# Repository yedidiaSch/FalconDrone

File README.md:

# FalconDrone - RTOS Based Flight Controller

## Project Overview
FalconDrone is an ongoing development of a quadcopter flight control system built from scratch using the **STM32F446RE (Nucleo)** platform. The project focuses on implementing high-performance real-time estimation and control algorithms within a **FreeRTOS** environment.

The current milestone focuses on a "Studio-Tethered" stabilization mode, ensuring the drone maintains its attitude (Roll/Pitch) while secured to a test bench.

## System Architecture
The firmware is designed with a modular, object-oriented approach in C++, emphasizing non-blocking operations and efficient resource management.

### Key Features
* **Real-Time Kernel:** Task management and scheduling via FreeRTOS.
* **Asynchronous I/O:** IMU (ICM-20948 or MPU6050) data acquisition using **I2C DMA** to minimize CPU overhead.
* **Thread-Safe Logging:** Custom UART logging mechanism utilizing **DMA** and FreeRTOS Queues for non-blocking telemetry.
* **Attitude Estimation:** Implementation of raw sensor data processing (Accelerometer and Gyroscope) for Roll/Pitch calculation.

## Hardware Stack
* **MCU:** STM32F446RE (ARM Cortex-M4 @ 180MHz)
* **IMU:** ICM-20948 on the carrier board (`hardware/carrier`), MPU6050 on the breadboard rig.
  Pick with `cmake --preset Debug -DFALCON_BOARD=CARRIER|BREADBOARD` (CARRIER is the default;
  it also selects the nRF24 radio, BREADBOARD the ESP-NOW bridge).
* **Frame:** F450 Quadcopter Frame
* **Motors:** A2212 1000KV Brushless Motors
* **ESCs:** 30A Brushless XXD
* **Power:** 3S Lipo 2200mAh 11.1V

## Software Stack
* **Language:** C++ / C
* **OS:** FreeRTOS
* **Framework:** STM32Cube HAL
* **Build System:** CMake
* **Development Env:** VS Code on Ubuntu

## Current Status: Attitude Estimation Phase
The system currently performs the following:
1.  Initializes hardware peripherals (I2C, UART, DMA, GPIO).
2.  Starts the FreeRTOS scheduler.
3.  Continuously streams 14-byte IMU data packets via DMA.
4.  Processes raw data into Euler angles (Roll and Pitch).

### Forthcoming Milestones
* **Sensor Fusion:** Implementation of a Complementary Filter or Kalman Filter to reduce accelerometer noise and gyroscope drift.
* **PID Control:** Development of the attitude control loop for motor speed regulation.
* **PWM Generation:** Utilizing Timer peripherals to drive ESCs.

## Setup and Installation

### Prerequisites
* GNU Arm Embedded Toolchain
* CMake (minimum 3.10)
* STM32CubeMX (for peripheral configuration)
* OpenOCD / ST-Link Utilities

### Building
```bash
mkdir build
cd build
cmake ..
make

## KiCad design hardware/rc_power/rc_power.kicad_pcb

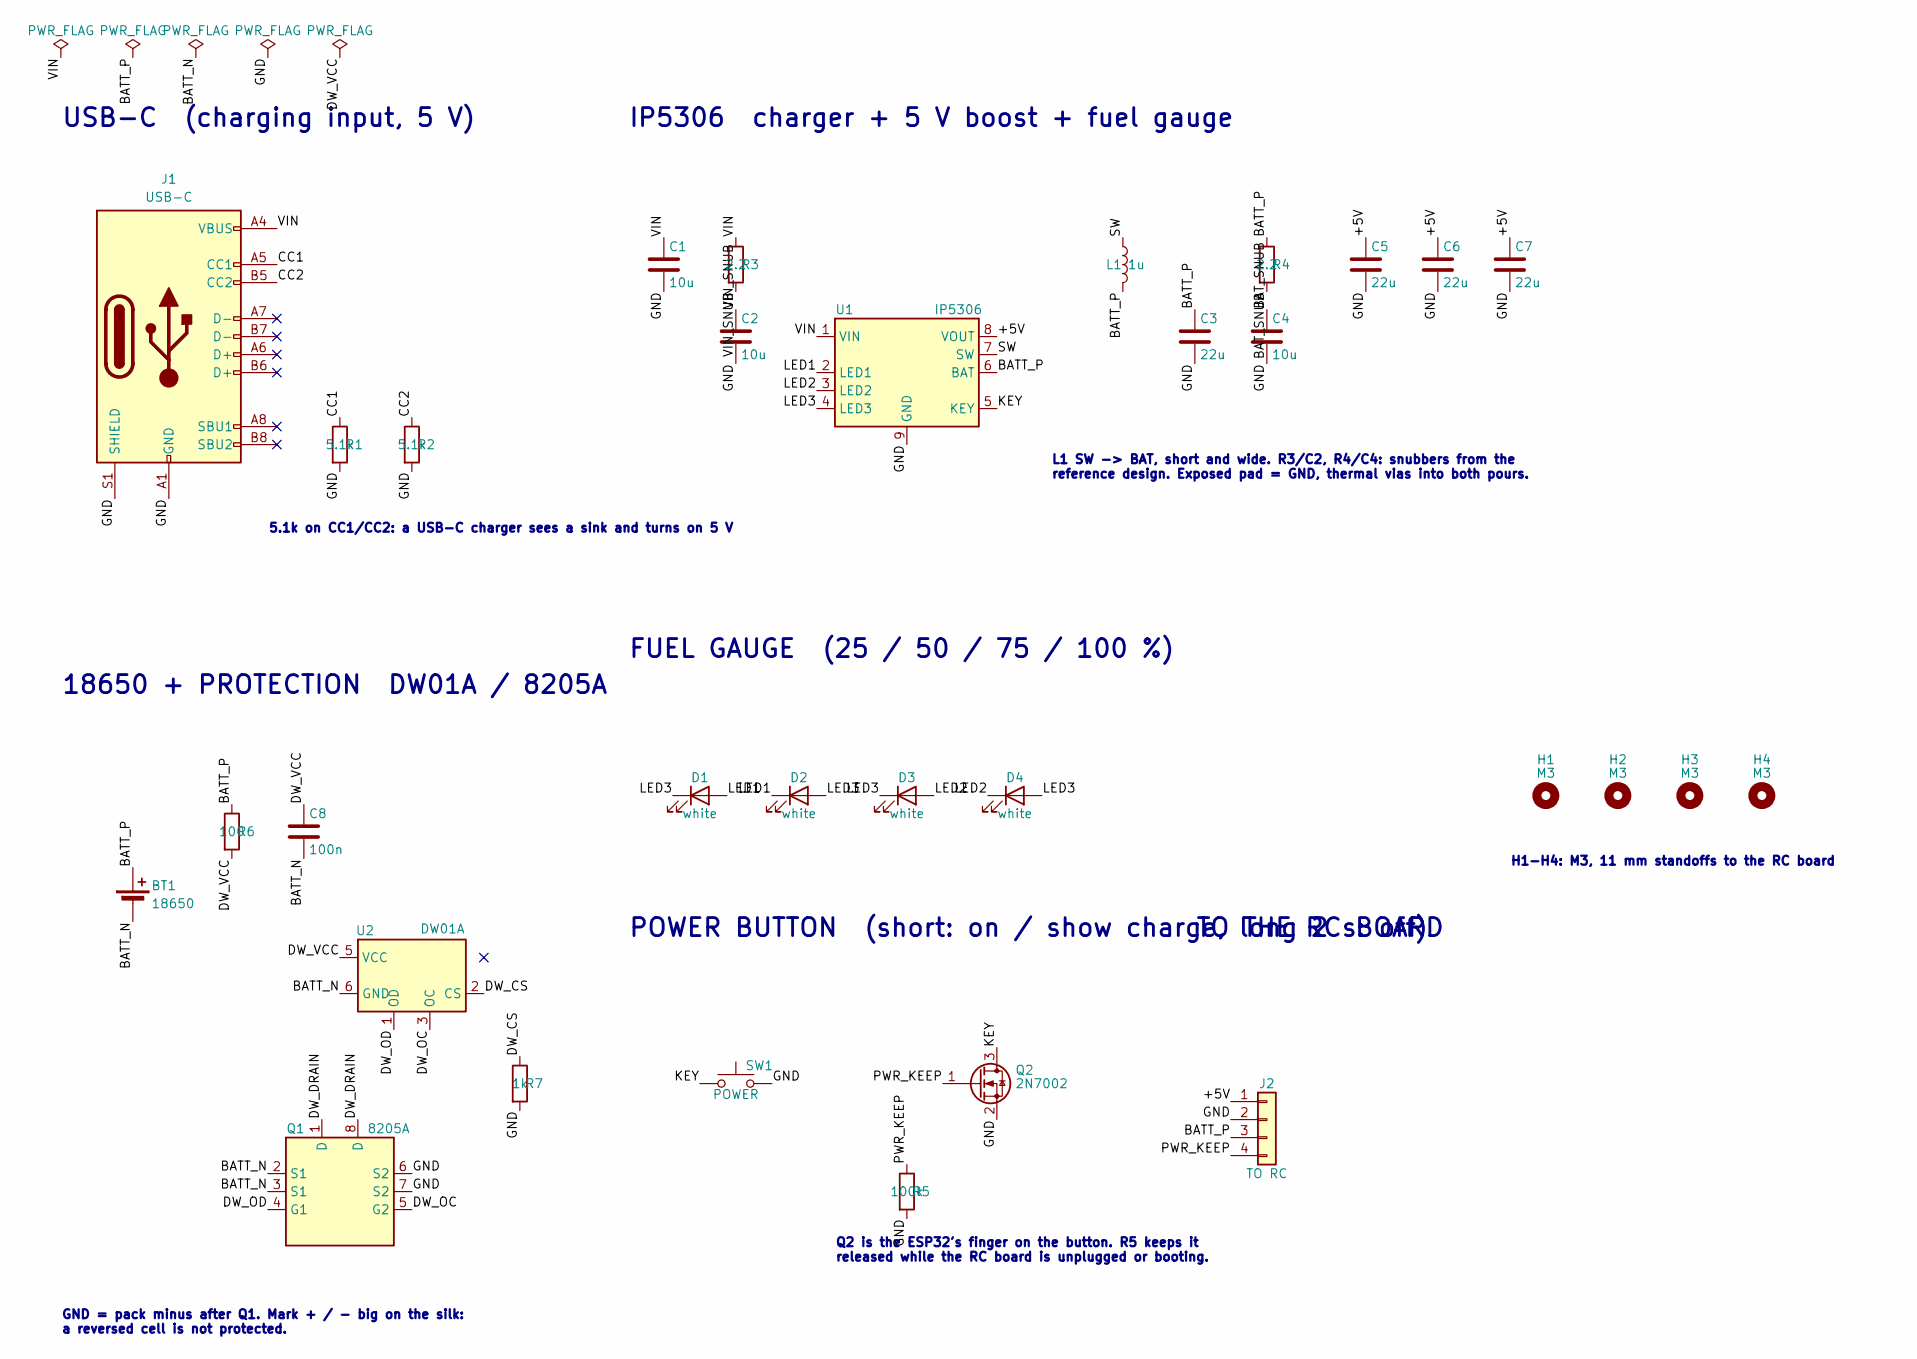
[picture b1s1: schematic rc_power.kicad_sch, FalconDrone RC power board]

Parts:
BT1: 18650; BatteryHolder_Keystone_1042_1x18650
C1, C2, C4: 10u; C_0805_2012Metric
C3, C5, C6, C7: 22u; C_0805_2012Metric
C8: 100n; C_0805_2012Metric
D1, D2, D3, D4: white; LED_0603_1608Metric
H1, H2, H3, H4: M3; MountingHole_3.2mm_M3
J1: USB-C; USB_C_Receptacle_HRO_TYPE-C-31-M-12
J2: TO RC; PinHeader_1x04_P2.54mm_Vertical
L1: 1u; L_Changjiang_FNR5020S
Q1: 8205A; TSSOP-8_4.4x3mm_P0.65mm
Q2: 2N7002; SOT-23
R1, R2: 5.1k; R_0805_2012Metric
R3, R4: 2.2; R_0805_2012Metric
R5: 100k; R_0805_2012Metric
R6: 100; R_0805_2012Metric
R7: 1k; R_0805_2012Metric
SW1: POWER; SW_Push_1P1T_XKB_TS-1187A
U1: IP5306; SOIC-8-1EP_3.9x4.9mm_P1.27mm_EP2.29x3mm_ThermalVias
U2: DW01A; SOT-23-6

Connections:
/+5V: C5.1, C6.1, C7.1, J2.1, U1.8 (VOUT)
/BATT_N: BT1.2 (-), C8.2, Q1.2 (S1), Q1.3 (S1), U2.6 (GND)
/BATT_P: BT1.1 (+), C3.1, J2.3, L1.2, R4.1, R6.1, U1.6 (BAT)
/BAT_SNUB: C4.1, R4.2
/CC1: J1.A5 (CC1), R1.1
/CC2: J1.B5 (CC2), R2.1
/DW_CS: R7.1, U2.2 (CS)
/DW_DRAIN: Q1.1 (D), Q1.8 (D)
/DW_OC: Q1.5 (G2), U2.3 (OC)
/DW_OD: Q1.4 (G1), U2.1 (OD)
/DW_VCC: C8.1, R6.2, U2.5 (VCC)
/GND: C1.2, C2.2, C3.2, C4.2, C5.2, C6.2, C7.2, J1.A1 (GND), J1.A12 (GND), J1.B1 (GND), J1.B12 (GND), J1.S1 (SHIELD), J2.2, Q1.6 (S2), Q1.7 (S2), Q2.2 (S), R1.2, R2.2, R5.2, R7.2, SW1.2, U1.9 (GND)
/KEY: Q2.3 (D), SW1.1, U1.5 (KEY)
/LED1: D1.2 (A), D2.1 (K), U1.2 (LED1)
/LED2: D3.2 (A), D4.1 (K), U1.3 (LED2)
/LED3: D1.1 (K), D2.2 (A), D3.1 (K), D4.2 (A), U1.4 (LED3)
/PWR_KEEP: J2.4, Q2.1 (G), R5.1
/SW: L1.1, U1.7 (SW)
/VIN: C1.1, J1.A4 (VBUS), J1.A9 (VBUS), J1.B4 (VBUS), J1.B9 (VBUS), R3.1, U1.1 (VIN)
/VIN_SNUB: C2.1, R3.2

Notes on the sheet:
USB-C (charging input, 5 V)
5.1k on CC1/CC2: a USB-C charger sees a sink and turns on 5 V
IP5306 charger + 5 V boost + fuel gauge
L1 SW -> BAT, short and wide. R3/C2, R4/C4: snubbers from the reference design. Exposed pad = GND, thermal vias into both pours.
FUEL GAUGE (25 / 50 / 75 / 100 %)
POWER BUTTON (short: on / show charge, long 2 s: off)
Q2 is the ESP32's finger on the button. R5 keeps it released while the RC board is unplugged or booting.
18650 + PROTECTION DW01A / 8205A
GND = pack minus after Q1. Mark + / - big on the silk: a reversed cell is not protected.
TO THE RC BOARD
H1-H4: M3, 11 mm standoffs to the RC board

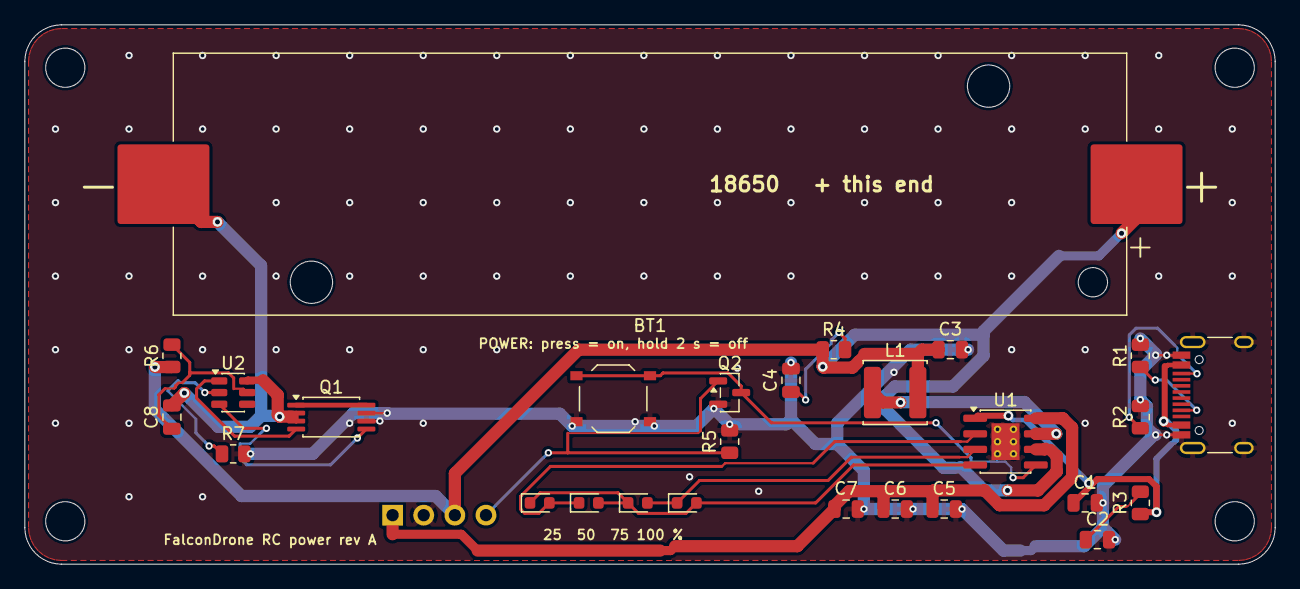
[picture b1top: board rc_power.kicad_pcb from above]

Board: 2 copper layers, 102.0 x 44.0 mm, 32 parts (1 on the bottom side), 20 nets.

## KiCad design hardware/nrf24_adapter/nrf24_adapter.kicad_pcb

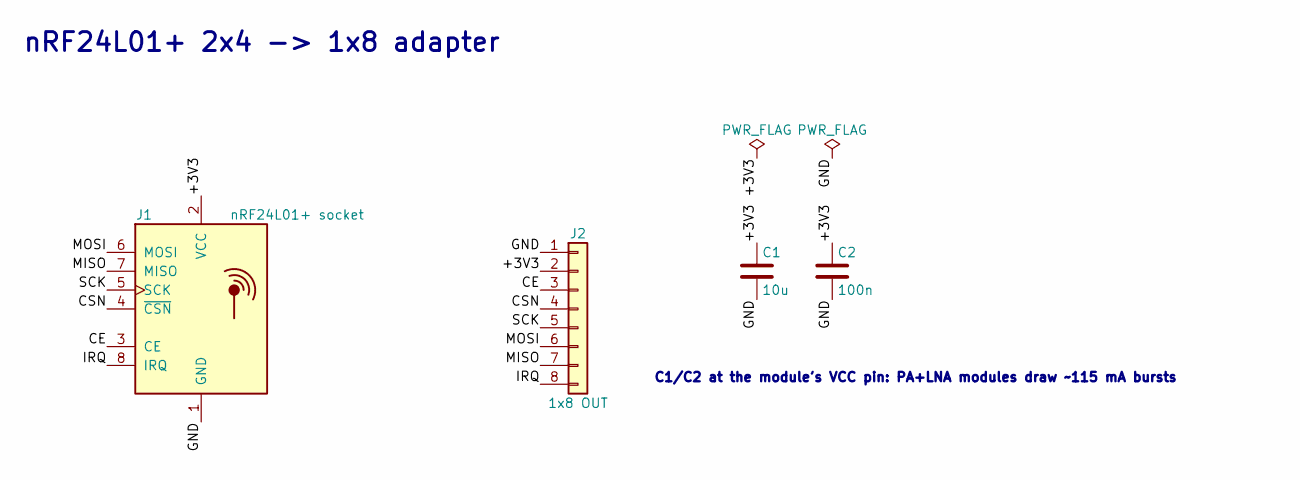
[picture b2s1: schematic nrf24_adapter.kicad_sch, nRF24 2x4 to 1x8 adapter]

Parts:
C1: 10u; C_0805_2012Metric_Pad1.18x1.45mm_HandSolder
C2: 100n; C_0805_2012Metric_Pad1.18x1.45mm_HandSolder
J1: nRF24L01+ socket; nRF24L01_Breakout
J2: 1x8 OUT; PinHeader_1x08_P2.54mm_Vertical

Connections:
/+3V3: C1.1, C2.1, J1.2 (VCC), J2.2
/CE: J1.3 (CE), J2.3
/CSN: J1.4 (~CSN), J2.4
/GND: C1.2, C2.2, J1.1 (GND), J2.1
/IRQ: J1.8 (IRQ), J2.8
/MISO: J1.7 (MISO), J2.7
/MOSI: J1.6 (MOSI), J2.6
/SCK: J1.5 (SCK), J2.5

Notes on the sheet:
nRF24L01+ 2x4 -> 1x8 adapter
C1/C2 at the module's VCC pin: PA+LNA modules draw ~115 mA bursts

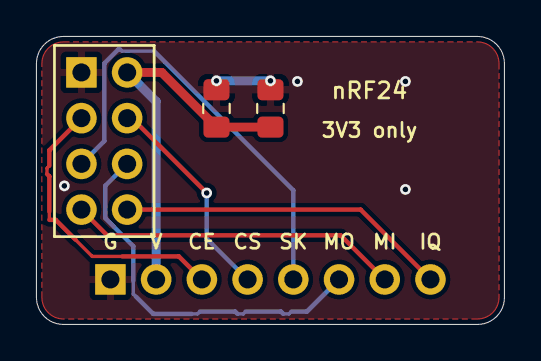
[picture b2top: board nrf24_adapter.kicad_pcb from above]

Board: 2 copper layers, 26.0 x 16.0 mm, 4 parts (1 on the bottom side), 8 nets.

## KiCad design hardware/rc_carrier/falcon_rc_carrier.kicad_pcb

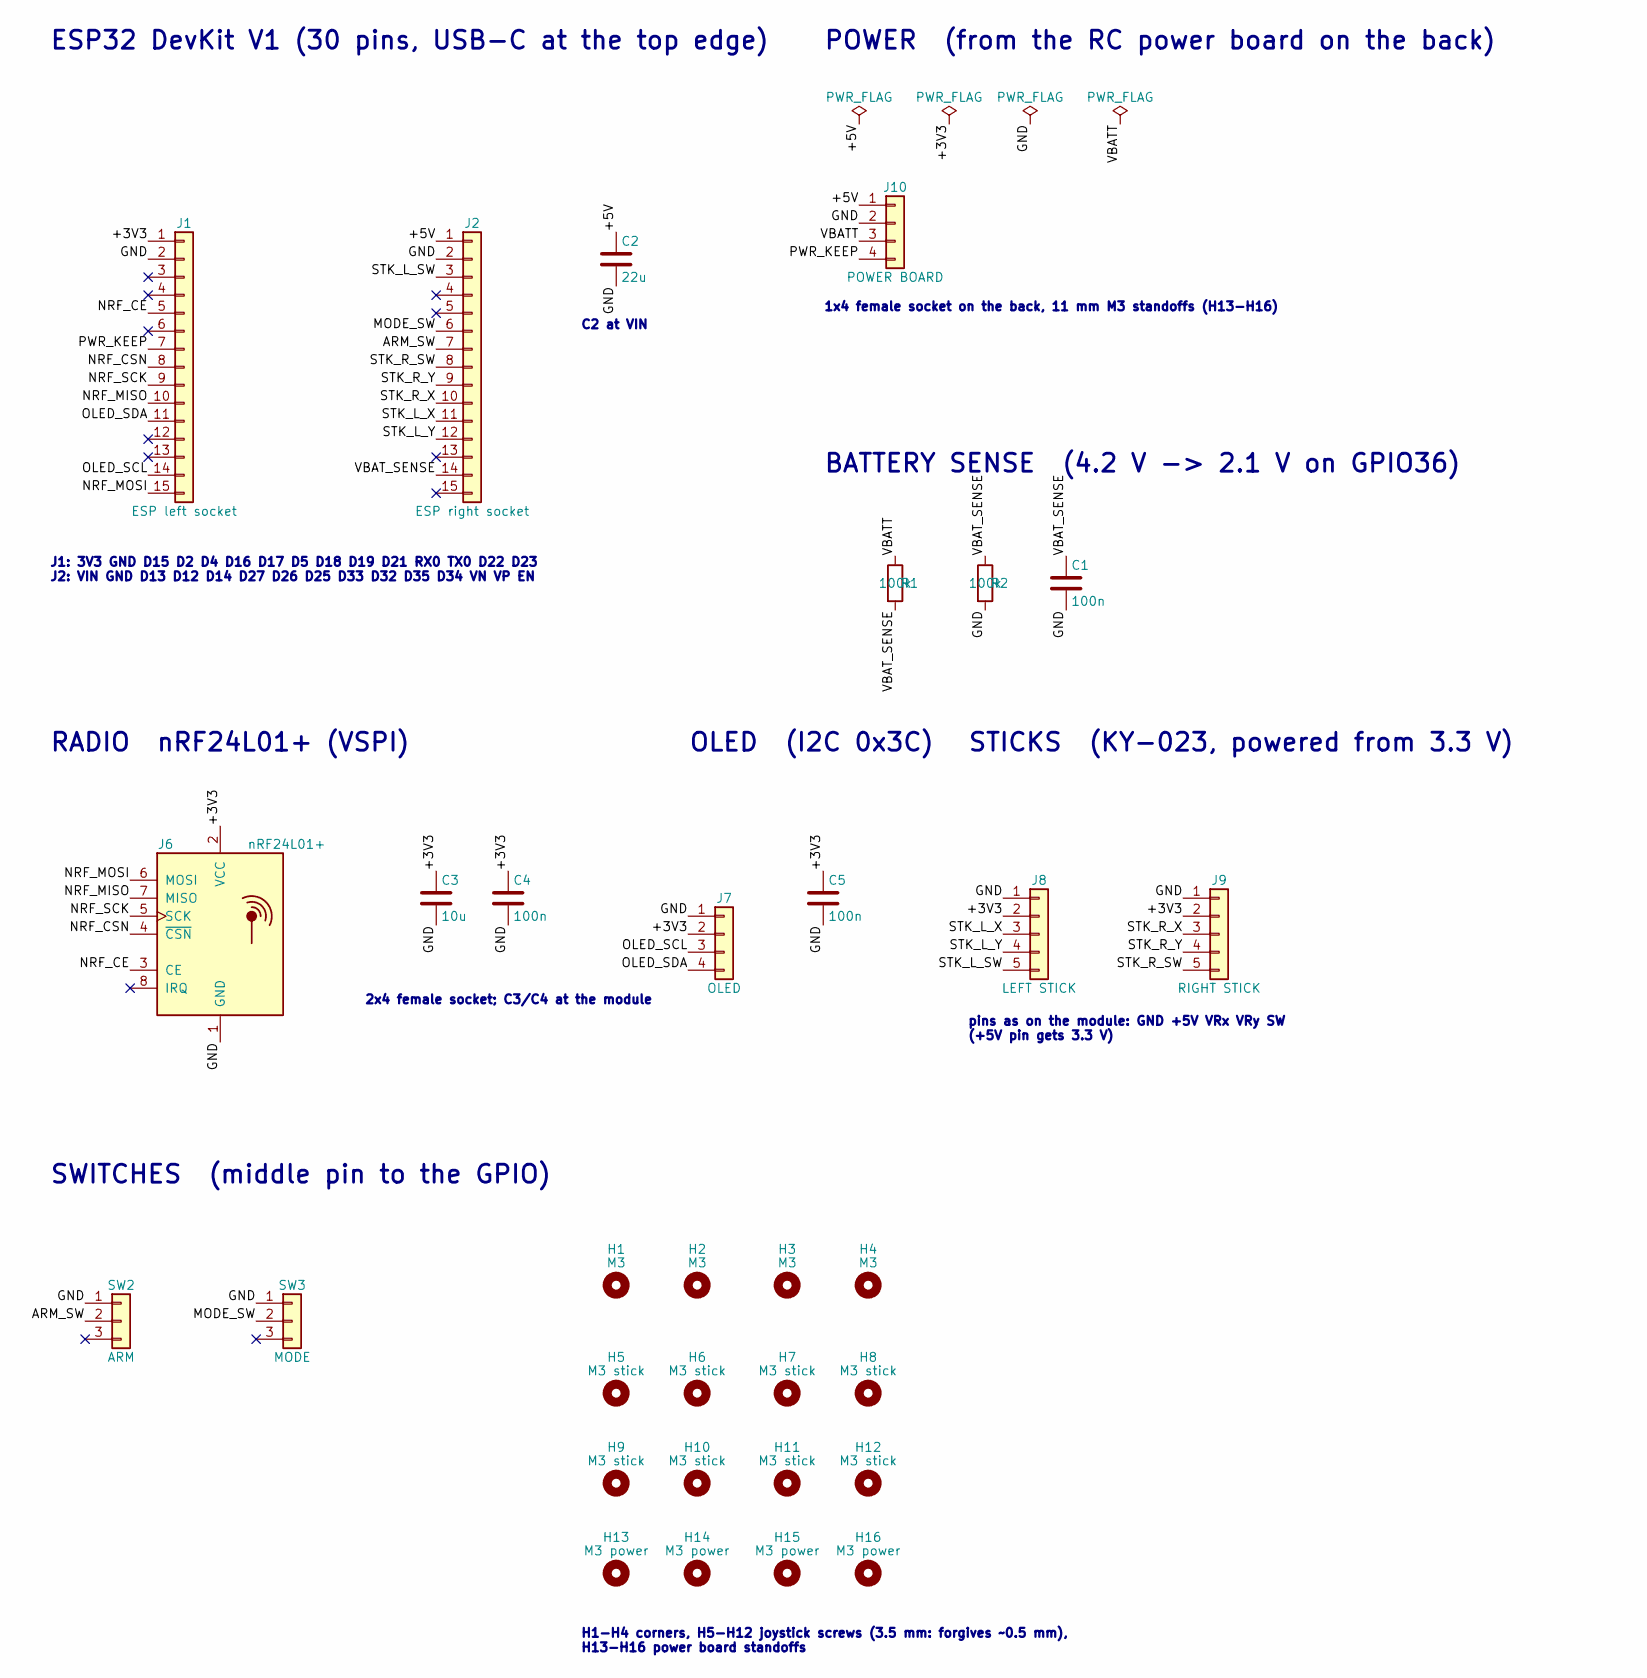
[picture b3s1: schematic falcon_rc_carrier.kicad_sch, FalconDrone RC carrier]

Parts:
C1, C4, C5: 100n; C_0805_2012Metric_Pad1.18x1.45mm_HandSolder
C2: 22u; C_0805_2012Metric_Pad1.18x1.45mm_HandSolder
C3: 10u; C_0805_2012Metric_Pad1.18x1.45mm_HandSolder
H1, H2, H3, H4: M3; MountingHole_3.2mm_M3
H5, H6, H7, H8, H9, H10, H11, H12: M3 stick; MountingHole_3.5mm
H13, H14, H15, H16: M3 power; MountingHole_3.2mm_M3
J1: ESP left socket; PinHeader_1x15_P2.54mm_Vertical
J2: ESP right socket; PinHeader_1x15_P2.54mm_Vertical
J6: nRF24L01+; nRF24L01_Breakout
J7: OLED; PinHeader_1x04_P2.54mm_Vertical
J8: LEFT STICK; PinHeader_1x05_P2.54mm_Vertical
J9: RIGHT STICK; PinHeader_1x05_P2.54mm_Vertical
J10: POWER BOARD; PinHeader_1x04_P2.54mm_Vertical
R1, R2: 100k; R_0805_2012Metric_Pad1.20x1.40mm_HandSolder
SW2: ARM; PinHeader_1x03_P2.54mm_Vertical
SW3: MODE; PinHeader_1x03_P2.54mm_Vertical

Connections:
/+3V3: C3.1, C4.1, C5.1, J1.1, J6.2 (VCC), J7.2, J8.2, J9.2
/+5V: C2.1, J2.1, J10.1
/ARM_SW: J2.7, SW2.2
/GND: C1.2, C2.2, C3.2, C4.2, C5.2, J1.2, J2.2, J6.1 (GND), J7.1, J8.1, J9.1, J10.2, R2.2, SW2.1, SW3.1
/MODE_SW: J2.6, SW3.2
/NRF_CE: J1.5, J6.3 (CE)
/NRF_CSN: J1.8, J6.4 (~CSN)
/NRF_MISO: J1.10, J6.7 (MISO)
/NRF_MOSI: J1.15, J6.6 (MOSI)
/NRF_SCK: J1.9, J6.5 (SCK)
/OLED_SCL: J1.14, J7.3
/OLED_SDA: J1.11, J7.4
/PWR_KEEP: J1.7, J10.4
/STK_L_SW: J2.3, J8.5
/STK_L_X: J2.11, J8.3
/STK_L_Y: J2.12, J8.4
/STK_R_SW: J2.8, J9.5
/STK_R_X: J2.10, J9.3
/STK_R_Y: J2.9, J9.4
/VBATT: J10.3, R1.1
/VBAT_SENSE: C1.1, J2.14, R1.2, R2.1

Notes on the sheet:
ESP32 DevKit V1 (30 pins, USB-C at the top edge)
J1: 3V3 GND D15 D2 D4 D16 D17 D5 D18 D19 D21 RX0 TX0 D22 D23 J2: VIN GND D13 D12 D14 D27 D26 D25 D33 D32 D35 D34 VN VP EN
C2 at VIN
POWER (from the RC power board on the back)
1x4 female socket on the back, 11 mm M3 standoffs (H13-H16)
BATTERY SENSE (4.2 V -> 2.1 V on GPIO36)
RADIO nRF24L01+ (VSPI)
2x4 female socket; C3/C4 at the module
OLED (I2C 0x3C)
STICKS (KY-023, powered from 3.3 V)
pins as on the module: GND +5V VRx VRy SW (+5V pin gets 3.3 V)
SWITCHES (middle pin to the GPIO)
H1-H4 corners, H5-H12 joystick screws (3.5 mm: forgives ~0.5 mm), H13-H16 power board standoffs

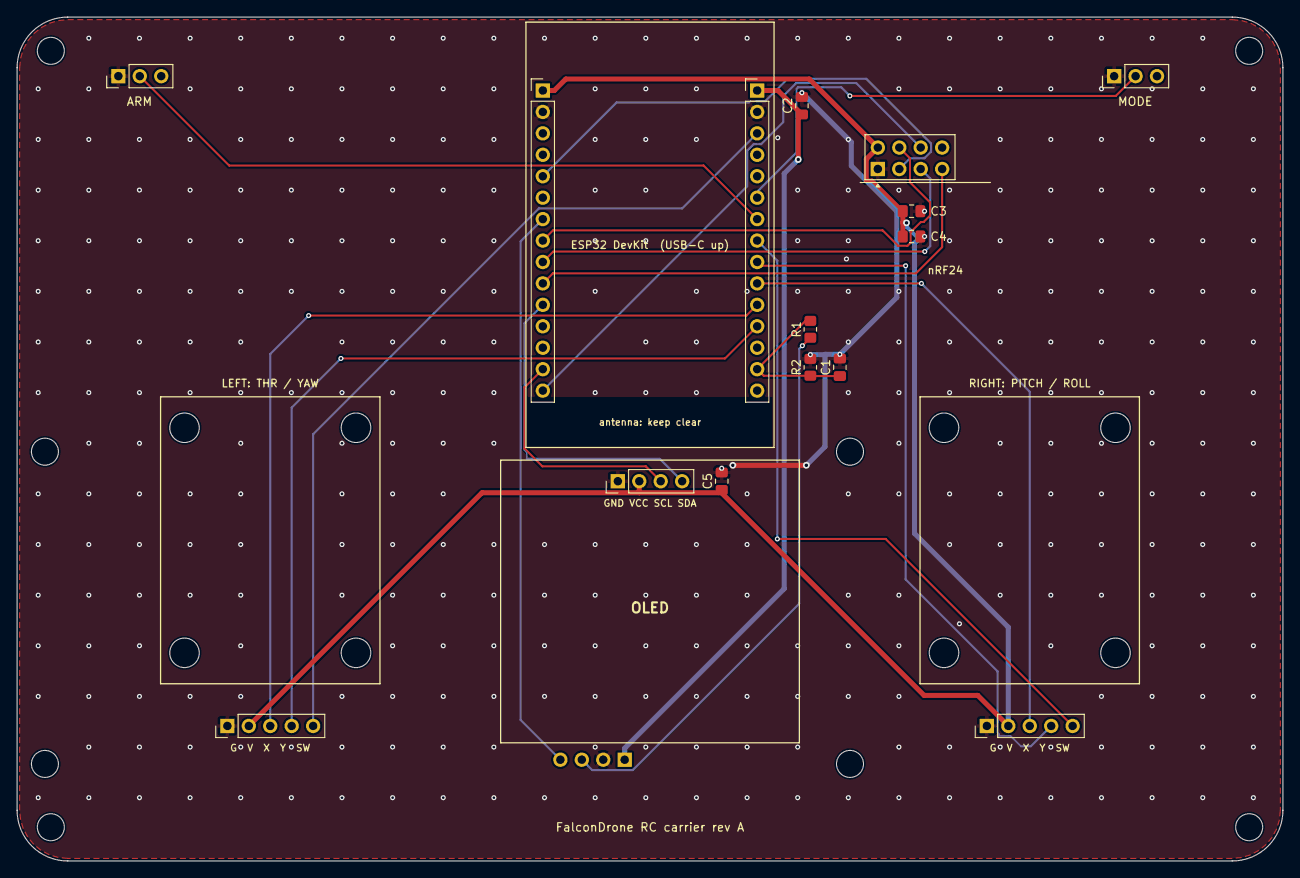
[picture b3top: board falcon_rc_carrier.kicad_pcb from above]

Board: 2 copper layers, 150.0 x 100.0 mm, 32 parts (1 on the bottom side), 21 nets.

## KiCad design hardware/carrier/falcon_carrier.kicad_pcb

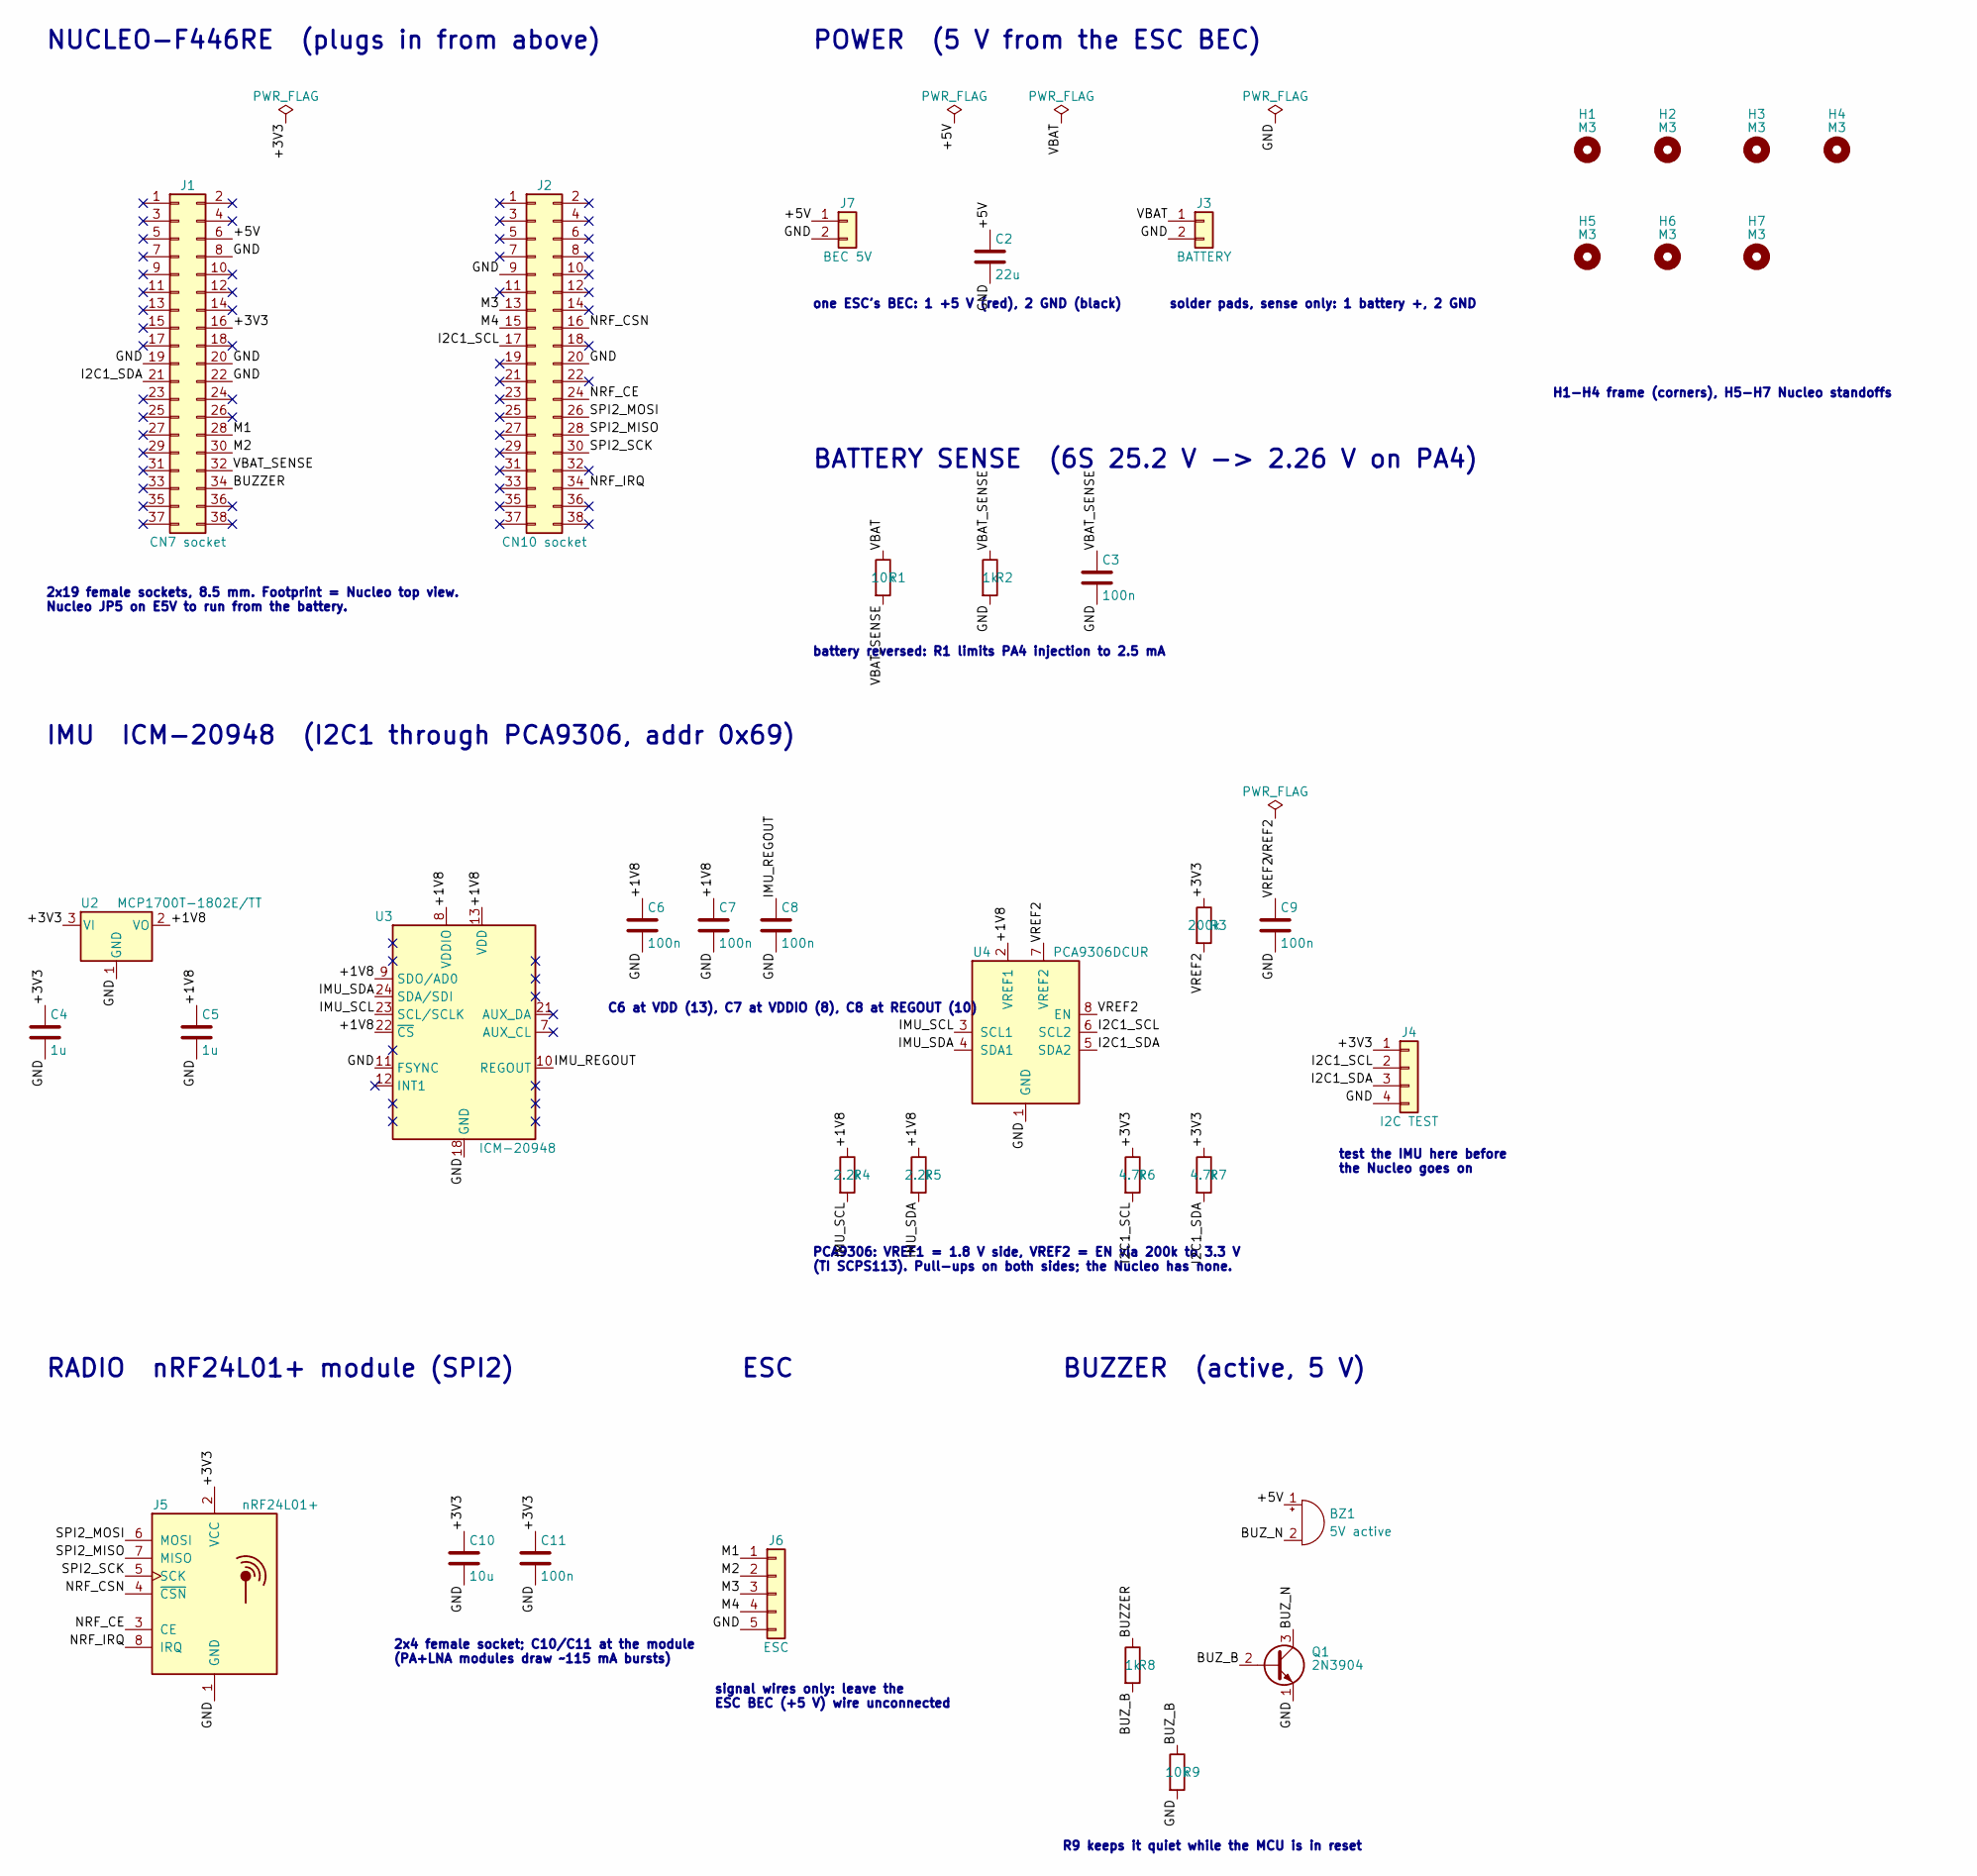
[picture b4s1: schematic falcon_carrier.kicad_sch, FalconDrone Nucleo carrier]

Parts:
BZ1: 5V active; Buzzer_12x9.5RM7.6
C2: 22u; C_0805_2012Metric_Pad1.18x1.45mm_HandSolder
C3, C6, C7, C8, C9, C11: 100n; C_0805_2012Metric_Pad1.18x1.45mm_HandSolder
C4, C5: 1u; C_0805_2012Metric_Pad1.18x1.45mm_HandSolder
C10: 10u; C_0805_2012Metric_Pad1.18x1.45mm_HandSolder
H1, H2, H3, H4, H5, H6, H7: M3; MountingHole_3.2mm_M3
J1: CN7 socket; PinHeader_2x19_P2.54mm_Vertical
J2: CN10 socket; PinHeader_2x19_P2.54mm_Vertical
J3: BATTERY; SolderWire-0.5sqmm_1x02_P4.8mm_D0.9mm_OD2.3mm
J4: I2C TEST; PinHeader_1x04_P2.54mm_Vertical
J5: nRF24L01+; nRF24L01_Breakout
J6: ESC; PinHeader_1x05_P2.54mm_Vertical
J7: BEC 5V; PinHeader_1x02_P2.54mm_Vertical
Q1: 2N3904; TO-92_Inline
R1, R9: 10k; R_Axial_DIN0207_L6.3mm_D2.5mm_P7.62mm_Horizontal
R2, R8: 1k; R_Axial_DIN0207_L6.3mm_D2.5mm_P7.62mm_Horizontal
R3: 200k; R_0805_2012Metric_Pad1.20x1.40mm_HandSolder
R4, R5: 2.2k; R_0805_2012Metric_Pad1.20x1.40mm_HandSolder
R6, R7: 4.7k; R_0805_2012Metric_Pad1.20x1.40mm_HandSolder
U2: MCP1700T-1802E/TT; SOT-23
U3: ICM-20948; InvenSense_QFN-24_3x3mm_P0.4mm
U4: PCA9306DCUR; VSSOP-8_2.3x2mm_P0.5mm

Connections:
/+1V8: C5.1, C6.1, C7.1, R4.1, R5.1, U2.2 (VO), U3.8 (VDDIO), U3.9 (SDO/AD0), U3.13 (VDD), U3.22 (~CS), U4.2 (VREF1)
/+3V3: C4.1, C10.1, C11.1, J1.16, J4.1, J5.2 (VCC), R3.1, R6.1, R7.1, U2.3 (VI)
/+5V: BZ1.1 (+), C2.1, J1.6, J7.1
/BUZZER: J1.34, R8.1
/BUZ_B: Q1.2 (B), R8.2, R9.1
/BUZ_N: BZ1.2 (-), Q1.3 (C)
/GND: C2.2, C3.2, C4.2, C5.2, C6.2, C7.2, C8.2, C9.2, C10.2, C11.2, J1.8, J1.19, J1.20, J1.22, J2.9, J2.20, J3.2, J4.4, J5.1 (GND), J6.5, J7.2, Q1.1 (E), R2.2, R9.2, U2.1 (GND), U3.11 (FSYNC), U3.18 (GND), U3.20 (GND), U4.1 (GND)
/I2C1_SCL: J2.17, J4.2, R6.2, U4.6 (SCL2)
/I2C1_SDA: J1.21, J4.3, R7.2, U4.5 (SDA2)
/IMU_REGOUT: C8.1, U3.10 (REGOUT)
/IMU_SCL: R4.2, U3.23 (SCL/SCLK), U4.3 (SCL1)
/IMU_SDA: R5.2, U3.24 (SDA/SDI), U4.4 (SDA1)
/M1: J1.28, J6.1
/M2: J1.30, J6.2
/M3: J2.13, J6.3
/M4: J2.15, J6.4
/NRF_CE: J2.24, J5.3 (CE)
/NRF_CSN: J2.16, J5.4 (~CSN)
/NRF_IRQ: J2.34, J5.8 (IRQ)
/SPI2_MISO: J2.28, J5.7 (MISO)
/SPI2_MOSI: J2.26, J5.6 (MOSI)
/SPI2_SCK: J2.30, J5.5 (SCK)
/VBAT: J3.1, R1.1
/VBAT_SENSE: C3.1, J1.32, R1.2, R2.1
/VREF2: C9.1, R3.2, U4.7 (VREF2), U4.8 (EN)

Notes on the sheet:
NUCLEO-F446RE (plugs in from above)
2x19 female sockets, 8.5 mm. Footprint = Nucleo top view. Nucleo JP5 on E5V to run from the battery.
POWER (5 V from the ESC BEC)
one ESC's BEC: 1 +5 V (red), 2 GND (black)
solder pads, sense only: 1 battery +, 2 GND
BATTERY SENSE (6S 25.2 V -> 2.26 V on PA4)
battery reversed: R1 limits PA4 injection to 2.5 mA
IMU ICM-20948 (I2C1 through PCA9306, addr 0x69)
C6 at VDD (13), C7 at VDDIO (8), C8 at REGOUT (10)
PCA9306: VREF1 = 1.8 V side, VREF2 = EN via 200k to 3.3 V (TI SCPS113). Pull-ups on both sides; the Nucleo has none.
test the IMU here before the Nucleo goes on
RADIO nRF24L01+ module (SPI2)
2x4 female socket; C10/C11 at the module (PA+LNA modules draw ~115 mA bursts)
ESC
signal wires only: leave the ESC BEC (+5 V) wire unconnected
BUZZER (active, 5 V)
R9 keeps it quiet while the MCU is in reset
H1-H4 frame (corners), H5-H7 Nucleo standoffs

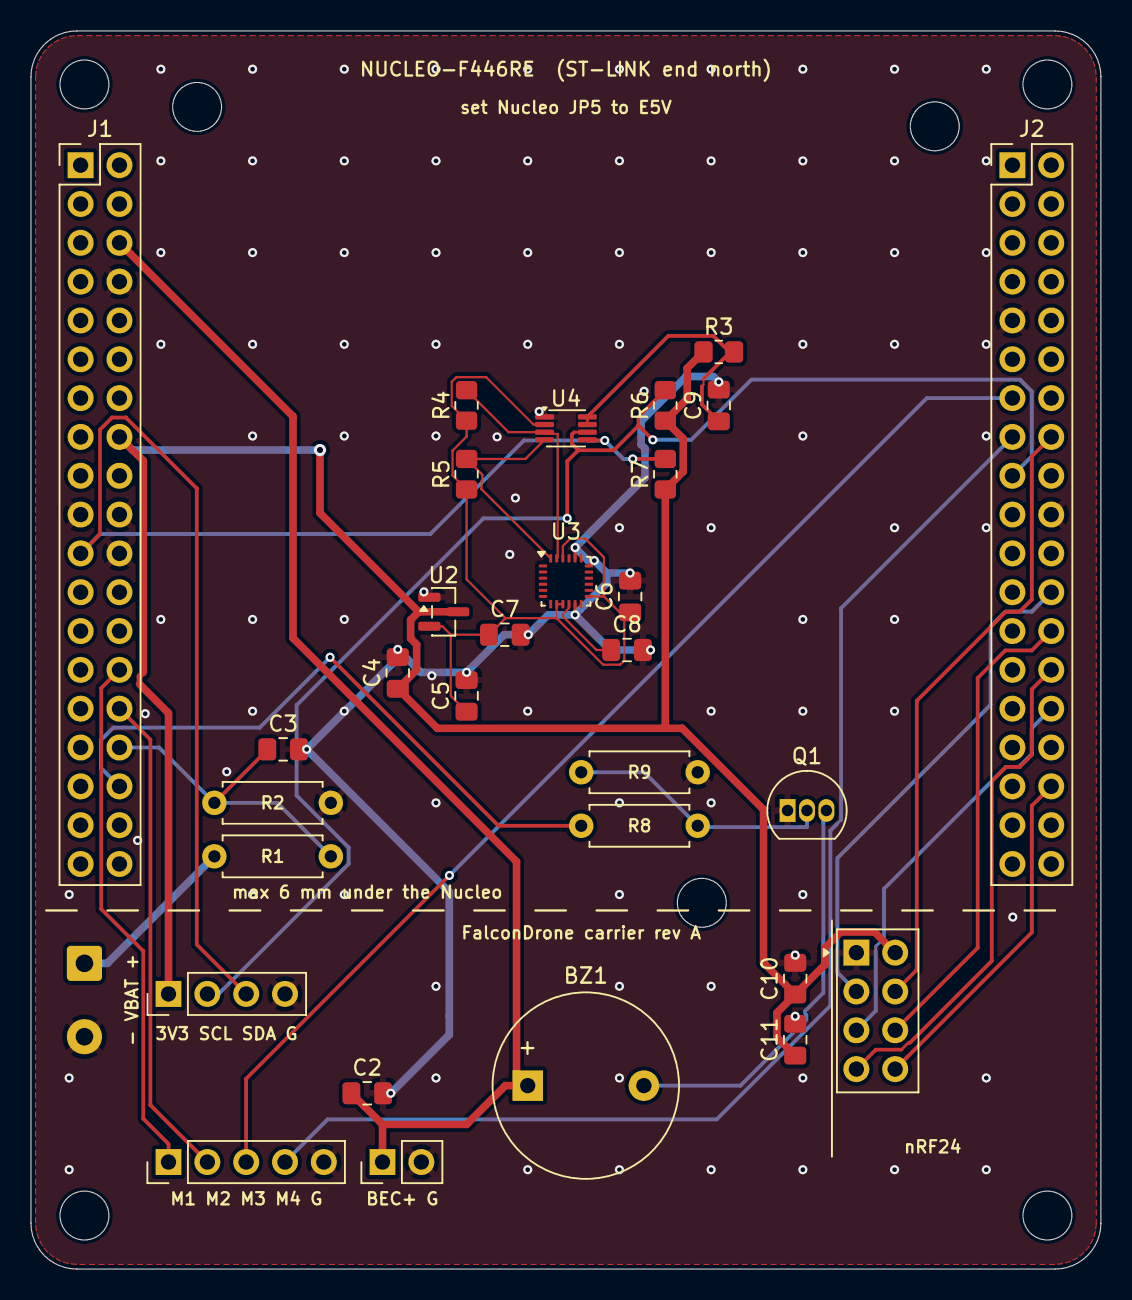
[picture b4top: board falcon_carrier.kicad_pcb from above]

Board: 2 copper layers, 70.0 x 81.0 mm, 38 parts (0 on the bottom side), 25 nets.
